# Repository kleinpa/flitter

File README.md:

# The Flitter Keyboard

Flitter is an minimalist unibody split keyboard with 42 keys. The layout is inspired by the [Corne](https://github.com/foostan/crkbd) keyboard but without the complexity of a fully split keyboard. It is built using my [keyboard-toolbox](https://github.com/kleinpa/keyboard-toolbox) which generates most design artifacts programatically from a tweakable keyboard definition.

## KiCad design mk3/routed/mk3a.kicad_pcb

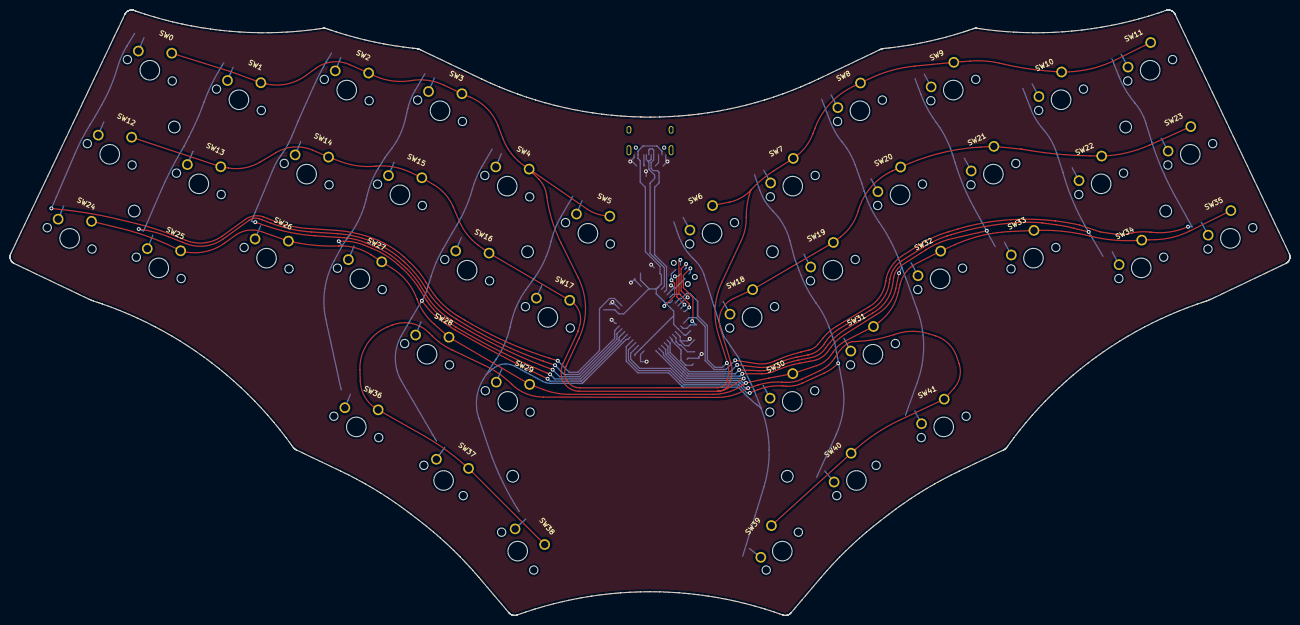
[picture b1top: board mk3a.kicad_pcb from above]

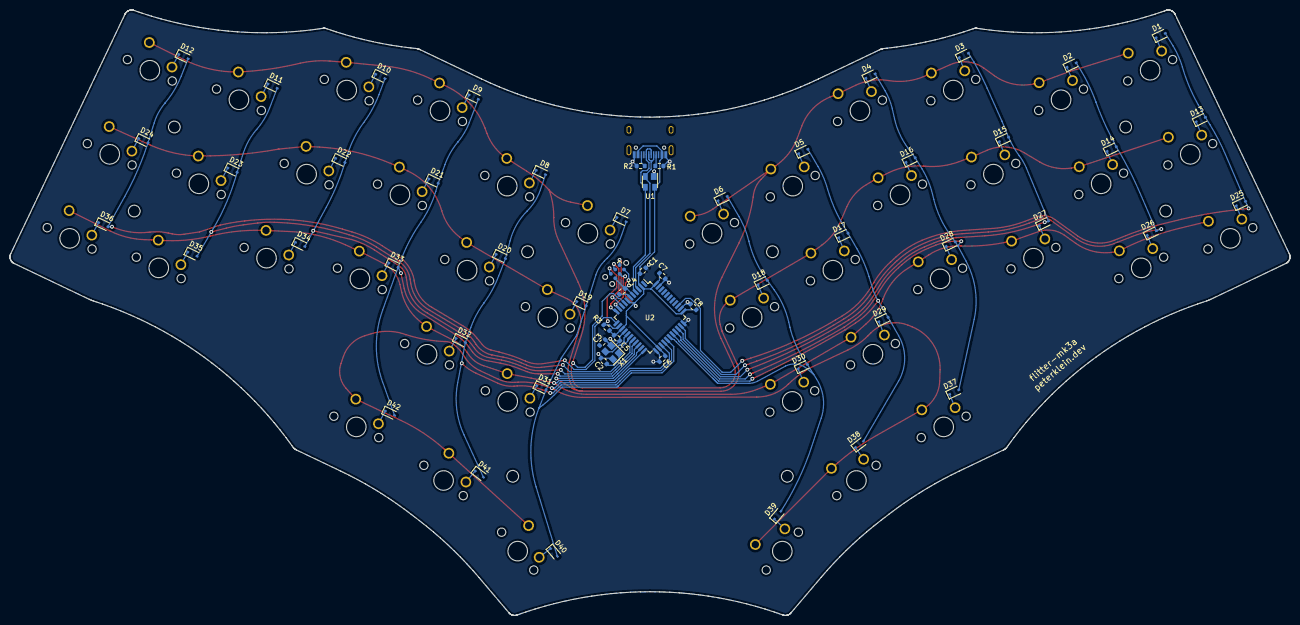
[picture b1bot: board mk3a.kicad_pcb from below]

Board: 2 copper layers, 261.8 x 123.9 mm, 100 parts (58 on the bottom side), 71 nets.

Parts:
C1: 10 µF; R_0603_1608Metric
C2, C3: 22 pF; R_0603_1608Metric
C4: 1 µF; R_0603_1608Metric
C5, C6, C7, C8: 0.1 µF; R_0603_1608Metric
D1, D2, D3, D4, D5, D6, D7, D8, D9, D10, D11, D12, D13, D14, D15, D16, D17, D18, D19, D20, D21, D22, D23, D24, D25, D26, D27, D28, D29, D30, D31, D32, D33, D34, D35, D36, D37, D38, D39, D40, D41, D42: 4148; D_SOD-323
J1: HRO-TYPE-C-31-M-12
Jx1: Tag-Connect_TC2030-IDC-NL_2x03_P1.27mm_Vertical
R1, R2: 5.1 kΩ; R_0603_1608Metric
R3: 10 kΩ; R_0603_1608Metric
SW0, SW1, SW2, SW3, SW4, SW5, SW6, SW7, SW8, SW9, SW10, SW11, SW12, SW13, SW14, SW15, SW16, SW17, SW18, SW19, SW20, SW21, SW22, SW23, SW24, SW25, SW26, SW27, SW28, SW29, SW30, SW31, SW32, SW33, SW34, SW35, SW36, SW37, SW38, SW39, SW40, SW41: SW_Cherry_MX_1.00u_PCB; SW_Cherry_MX_PCB
U1: SR05; SOT-143
U2: ATMEGA32U4-AU; TQFP-44_10x10mm_P0.8mm
X1: 16 MHz; Crystal_SMD_3225-4Pin_3.2x2.5mm

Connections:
GND: C1.1, C2.2, C3.2, C4.1, C5.1, C6.2, C7.1, C8.2, J1.1, J1.12, Jx1.6, R1.1, R2.2, U1.1, U2.5, U2.15, U2.23, U2.33, U2.35, U2.43, X1.2, X1.4
icsp-miso: Jx1.1, U2.11
icsp-mosi: Jx1.4, U2.10
icsp-reset: Jx1.5, R3.2, U2.13
icsp-sck: Jx1.3, U2.9
matrix-0: SW0.1, SW1.1, SW2.1, SW3.1, SW4.1, SW5.1, SW6.1, SW7.1, SW8.1, SW9.1, SW10.1, SW11.1, U2.8
matrix-3: D12.2, D24.2, D36.2, U2.12
matrix-4: D11.2, D23.2, D35.2, U2.18
matrix-5: D10.2, D22.2, D34.2, U2.19
matrix-6: D9.2, D21.2, D33.2, D42.2, U2.20
matrix-7: SW12.1, SW13.1, SW14.1, SW15.1, SW16.1, SW17.1, SW18.1, SW19.1, SW20.1, SW21.1, SW22.1, SW23.1, U2.21
matrix-8: SW24.1, SW25.1, SW26.1, SW27.1, SW28.1, SW29.1, SW30.1, SW31.1, SW32.1, SW33.1, SW34.1, SW35.1, U2.22
matrix-9: SW36.1, SW37.1, SW38.1, SW39.1, SW40.1, SW41.1, U2.25
matrix-10: D8.2, D20.2, D32.2, D41.2, U2.26
matrix-11: D7.2, D19.2, D31.2, D40.2, U2.27
matrix-12: D6.2, D18.2, D30.2, D39.2, U2.28
matrix-13: D5.2, D17.2, D29.2, D38.2, U2.29
matrix-14: D4.2, D16.2, D28.2, D37.2, U2.30
matrix-15: D3.2, D15.2, D27.2, U2.31
matrix-16: D2.2, D14.2, D26.2, U2.32
matrix-17: D1.2, D13.2, D25.2, U2.36
switch-diode-0: D1.1, SW0.2
switch-diode-1: D2.1, SW1.2
switch-diode-2: D3.1, SW2.2
switch-diode-3: D4.1, SW3.2
switch-diode-4: D5.1, SW4.2
switch-diode-5: D6.1, SW5.2
switch-diode-6: D7.1, SW6.2
switch-diode-7: D8.1, SW7.2
switch-diode-8: D9.1, SW8.2
switch-diode-9: D10.1, SW9.2
switch-diode-10: D11.1, SW10.2
switch-diode-11: D12.1, SW11.2
switch-diode-12: D13.1, SW12.2
switch-diode-13: D14.1, SW13.2
switch-diode-14: D15.1, SW14.2
switch-diode-15: D16.1, SW15.2
switch-diode-16: D17.1, SW16.2
switch-diode-17: D18.1, SW17.2
switch-diode-18: D19.1, SW18.2
switch-diode-19: D20.1, SW19.2
switch-diode-20: D21.1, SW20.2
switch-diode-21: D22.1, SW21.2
switch-diode-22: D23.1, SW22.2
switch-diode-23: D24.1, SW23.2
switch-diode-24: D25.1, SW24.2
switch-diode-25: D26.1, SW25.2
switch-diode-26: D27.1, SW26.2
switch-diode-27: D28.1, SW27.2
switch-diode-28: D29.1, SW28.2
switch-diode-29: D30.1, SW29.2
switch-diode-30: D31.1, SW30.2
switch-diode-31: D32.1, SW31.2
switch-diode-32: D33.1, SW32.2
switch-diode-33: D34.1, SW33.2
switch-diode-34: D35.1, SW34.2
switch-diode-35: D36.1, SW35.2
switch-diode-36: D37.1, SW36.2
switch-diode-37: D38.1, SW37.2
switch-diode-38: D39.1, SW38.2
switch-diode-39: D40.1, SW39.2
switch-diode-40: D41.1, SW40.2
switch-diode-41: D42.1, SW41.2
ucap: C4.2, U2.6
usb-cc1: J1.4, R1.2
usb-cc2: J1.10, R2.1
usb-dn: J1.5, J1.7, U1.2, U2.3
usb-dp: J1.6, J1.8, U1.3, U2.4
usb-vcc: C1.2, C5.2, C6.1, C7.2, C8.1, J1.2, J1.11, Jx1.2, R3.1, U1.4, U2.2, U2.7, U2.14, U2.24, U2.34, U2.44
xtal1: C2.1, U2.17, X1.1
xtal2: C3.1, U2.16, X1.3

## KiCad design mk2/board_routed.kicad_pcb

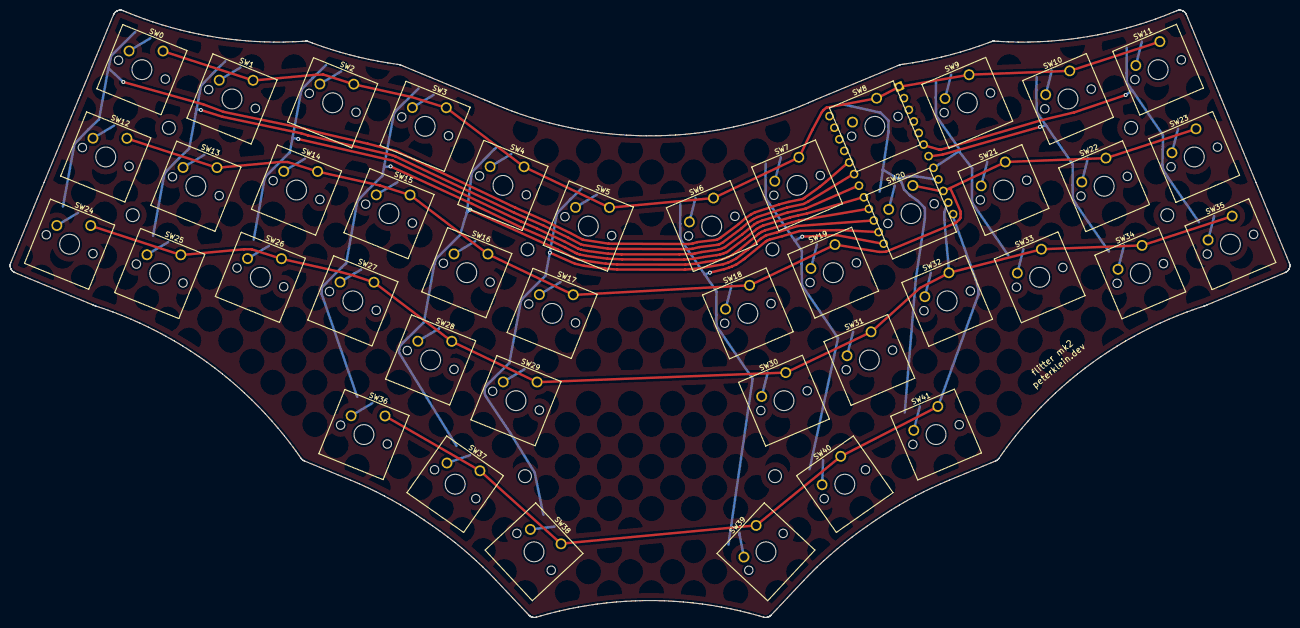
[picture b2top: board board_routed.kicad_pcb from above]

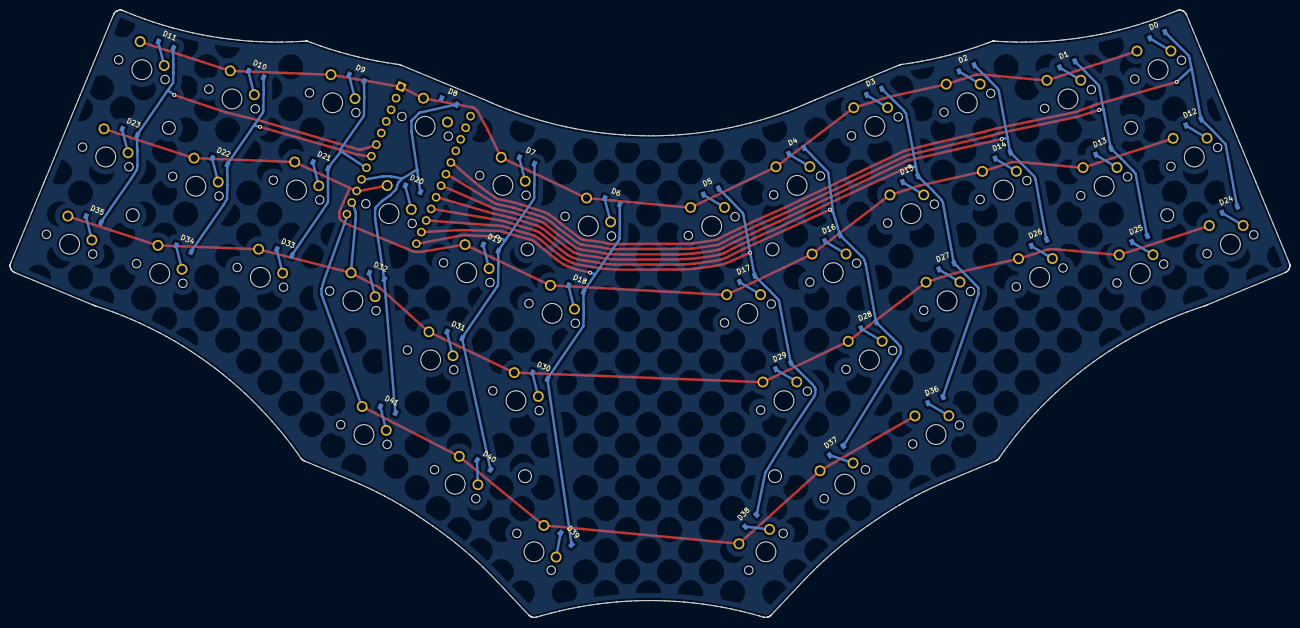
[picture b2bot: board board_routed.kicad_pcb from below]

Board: 2 copper layers, 258.1 x 122.5 mm, 85 parts (43 on the bottom side), 59 nets.

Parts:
D0, D1, D2, D3, D4, D5, D6, D7, D8, D9, D10, D11, D12, D13, D14, D15, D16, D17, D18, D19, D20, D21, D22, D23, D24, D25, D26, D27, D28, D29, D30, D31, D32, D33, D34, D35, D36, D37, D38, D39, D40, D41: 4148; D_SOD-123
MCU0: ProMicro; ArduinoProMicro
SW0, SW1, SW2, SW3, SW4, SW5, SW6, SW7, SW8, SW9, SW10, SW11, SW12, SW13, SW14, SW15, SW16, SW17, SW18, SW19, SW20, SW21, SW22, SW23, SW24, SW25, SW26, SW27, SW28, SW29, SW30, SW31, SW32, SW33, SW34, SW35, SW36, SW37, SW38, SW39, SW40, SW41: SW_Cherry_MX_1.00u_PCB

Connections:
GND: MCU0.3, MCU0.4, MCU0.23
io-0: MCU0.1, SW0.1, SW1.1, SW2.1, SW3.1, SW4.1, SW5.1, SW6.1, SW7.1, SW8.1, SW9.1, SW10.1, SW11.1
io-3: D11.2, D23.2, D35.2, MCU0.6
io-4: D10.2, D22.2, D34.2, MCU0.7
io-5: D9.2, D21.2, D33.2, MCU0.8
io-6: D8.2, D20.2, D32.2, D41.2, MCU0.9
io-7: MCU0.10, SW12.1, SW13.1, SW14.1, SW15.1, SW16.1, SW17.1, SW18.1, SW19.1, SW20.1, SW21.1, SW22.1, SW23.1
io-8: MCU0.11, SW24.1, SW25.1, SW26.1, SW27.1, SW28.1, SW29.1, SW30.1, SW31.1, SW32.1, SW33.1, SW34.1, SW35.1
io-9: MCU0.12, SW36.1, SW37.1, SW38.1, SW39.1, SW40.1, SW41.1
io-10: D7.2, D19.2, D31.2, D40.2, MCU0.13
io-11: D6.2, D18.2, D30.2, D39.2, MCU0.14
io-12: D5.2, D17.2, D29.2, D38.2, MCU0.15
io-13: D4.2, D16.2, D28.2, D37.2, MCU0.16
io-14: D3.2, D15.2, D27.2, D36.2, MCU0.17
io-15: D2.2, D14.2, D26.2, MCU0.18
io-16: D1.2, D13.2, D25.2, MCU0.19
io-17: D0.2, D12.2, D24.2, MCU0.20
switch-diode-0: D0.1, SW0.2
switch-diode-1: D1.1, SW1.2
switch-diode-2: D2.1, SW2.2
switch-diode-3: D3.1, SW3.2
switch-diode-4: D4.1, SW4.2
switch-diode-5: D5.1, SW5.2
switch-diode-6: D6.1, SW6.2
switch-diode-7: D7.1, SW7.2
switch-diode-8: D8.1, SW8.2
switch-diode-9: D9.1, SW9.2
switch-diode-10: D10.1, SW10.2
switch-diode-11: D11.1, SW11.2
switch-diode-12: D12.1, SW12.2
switch-diode-13: D13.1, SW13.2
switch-diode-14: D14.1, SW14.2
switch-diode-15: D15.1, SW15.2
switch-diode-16: D16.1, SW16.2
switch-diode-17: D17.1, SW17.2
switch-diode-18: D18.1, SW18.2
switch-diode-19: D19.1, SW19.2
switch-diode-20: D20.1, SW20.2
switch-diode-21: D21.1, SW21.2
switch-diode-22: D22.1, SW22.2
switch-diode-23: D23.1, SW23.2
switch-diode-24: D24.1, SW24.2
switch-diode-25: D25.1, SW25.2
switch-diode-26: D26.1, SW26.2
switch-diode-27: D27.1, SW27.2
switch-diode-28: D28.1, SW28.2
switch-diode-29: D29.1, SW29.2
switch-diode-30: D30.1, SW30.2
switch-diode-31: D31.1, SW31.2
switch-diode-32: D32.1, SW32.2
switch-diode-33: D33.1, SW33.2
switch-diode-34: D34.1, SW34.2
switch-diode-35: D35.1, SW35.2
switch-diode-36: D36.1, SW36.2
switch-diode-37: D37.1, SW37.2
switch-diode-38: D38.1, SW38.2
switch-diode-39: D39.1, SW39.2
switch-diode-40: D40.1, SW40.2
switch-diode-41: D41.1, SW41.2

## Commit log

2021-05-03 Intial commit
2021-05-03 Add routed mk2 PCB
2021-05-03 Add mk3 layout
2021-05-12 Update layout generation
2021-05-20 Branding
2021-05-20 Update kleinpa/keyboard-toolkit
2021-06-01 Update kleinpa/keyboard-toolkit and add BOM generation
2021-06-13 Update image URL
2021-07-06 Update keyboard-toolbox
2021-07-07 Add mk3a and mk3s keyboards
2021-07-07 Partially port to keyboard-toolbox
2021-07-07 Add comparison between mk3 and earlier layouts
